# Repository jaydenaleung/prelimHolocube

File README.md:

Holocube
===

A volumetric display from stacked transparent displays as a premise to a true free-floating voxel-array display.

---

## Overview

Holocube is a volumetric (three dimensional) display that utilizes transparent OLED display modules placed on top of each other to create a 128 by 128 by 8 pixel array. The goal of this project is to make a plain, electrical engineering-focused "hologram solution" before attempting to build a more theoretical or physics-based model for three-dimensional displays. The device is primarily run through an Arduino/ESP32-style microcontroller.

**Total time spent: 100+ hrs**

## Why I Created This Project

As suggested above, I am working on a larger personal project to realize three-dimensional display technology (commonly referred to as "holograms"). This provides a simple, stripped-down, preliminary solution to a more complex physics-based approach. Aside from that, it provides an easier solution to popularizing practical three-dimensional technology. Moreover, I simply love sci-fi and holograms and believe in their highly applicable potential, leading me to embark on this project.

## How It Works & Implementation

This device utilizes eight "stacked" transparent OLED displays from the Surenoo dealer on Aliexpress. The transparent OLED displays are driven using 12V external power, 3.3V logic, and SPI communication with an ESP32. The IC within the display is the SH1107 IC. The ESP32 uses either the Adafruit_SH110X + Adafruit_GFX, U8g2_lib, or SPI Arduino IDE library to send the specific SPI commands to drive the OLED panels. The datasheet specifies an external application circuit that includes external capacitors and resistors. See the datasheet for more information. The case was built using the Onshape CAD software.

A log of my testing can be found in the Word document in this repository.

NOTE: The markings on the PCB adapter that come with the transparent OLED display are incorrect. Refer to the PCB for the correct pin markings, with the display output pads always facing up and away from the PCB.

## Rough Bill of Materials (BOM)

| **Name** | **Quantity** | **Price (per part)** | **Link** |
| --- | --- | --- | --- |
| Transparent OLED Display | 8   | $10.15125 | [aliexpress.us/item/3256807797385510.html](https://www.aliexpress.us/item/3256807797385510.html) |
| PCB from JLCPCB | 5 (minimum order qty) | $3.42 | [jlcpcb.com](jlcpcb.com) |
| 30-Pin ESP-32 (28.2 x 51.4 mm) | 1   | $5.11 | [https://www.aliexpress.us/item/3256806034074322.html](https://www.aliexpress.us/item/3256806034074322.html) |
| 12V Power Source/Battery | 1   | $4.87 | [https://www.aliexpress.us/item/3256806309380899.html](https://www.aliexpress.us/item/3256806309380899.html) |
| 1μF Ceramic Capacitor | 8   | $0.033333 | [https://www.amazon.com/BOJACK-Capacitor-Multilayer-Monolithic-Assortment/dp/B085RDTCCV/](https://www.amazon.com/BOJACK-Capacitor-Multilayer-Monolithic-Assortment/dp/B085RDTCCV/) |
| 4.7μF Electrolytic Capacitor | 16  | $0.041667 | [https://www.amazon.com/ALLECIN-Electrolytic-Capacitor-Assortment-Kit/dp/B0C1VBXCQM/](https://www.amazon.com/ALLECIN-Electrolytic-Capacitor-Assortment-Kit/dp/B0C1VBXCQM/) |
| 1MΩ Resistor | 8   | $0.01 | [https://www.amazon.com/BOJACK-Values-Resistor-Resistors-Assortment/dp/B08FD1XVL6/](https://www.amazon.com/BOJACK-Values-Resistor-Resistors-Assortment/dp/B08FD1XVL6/) |

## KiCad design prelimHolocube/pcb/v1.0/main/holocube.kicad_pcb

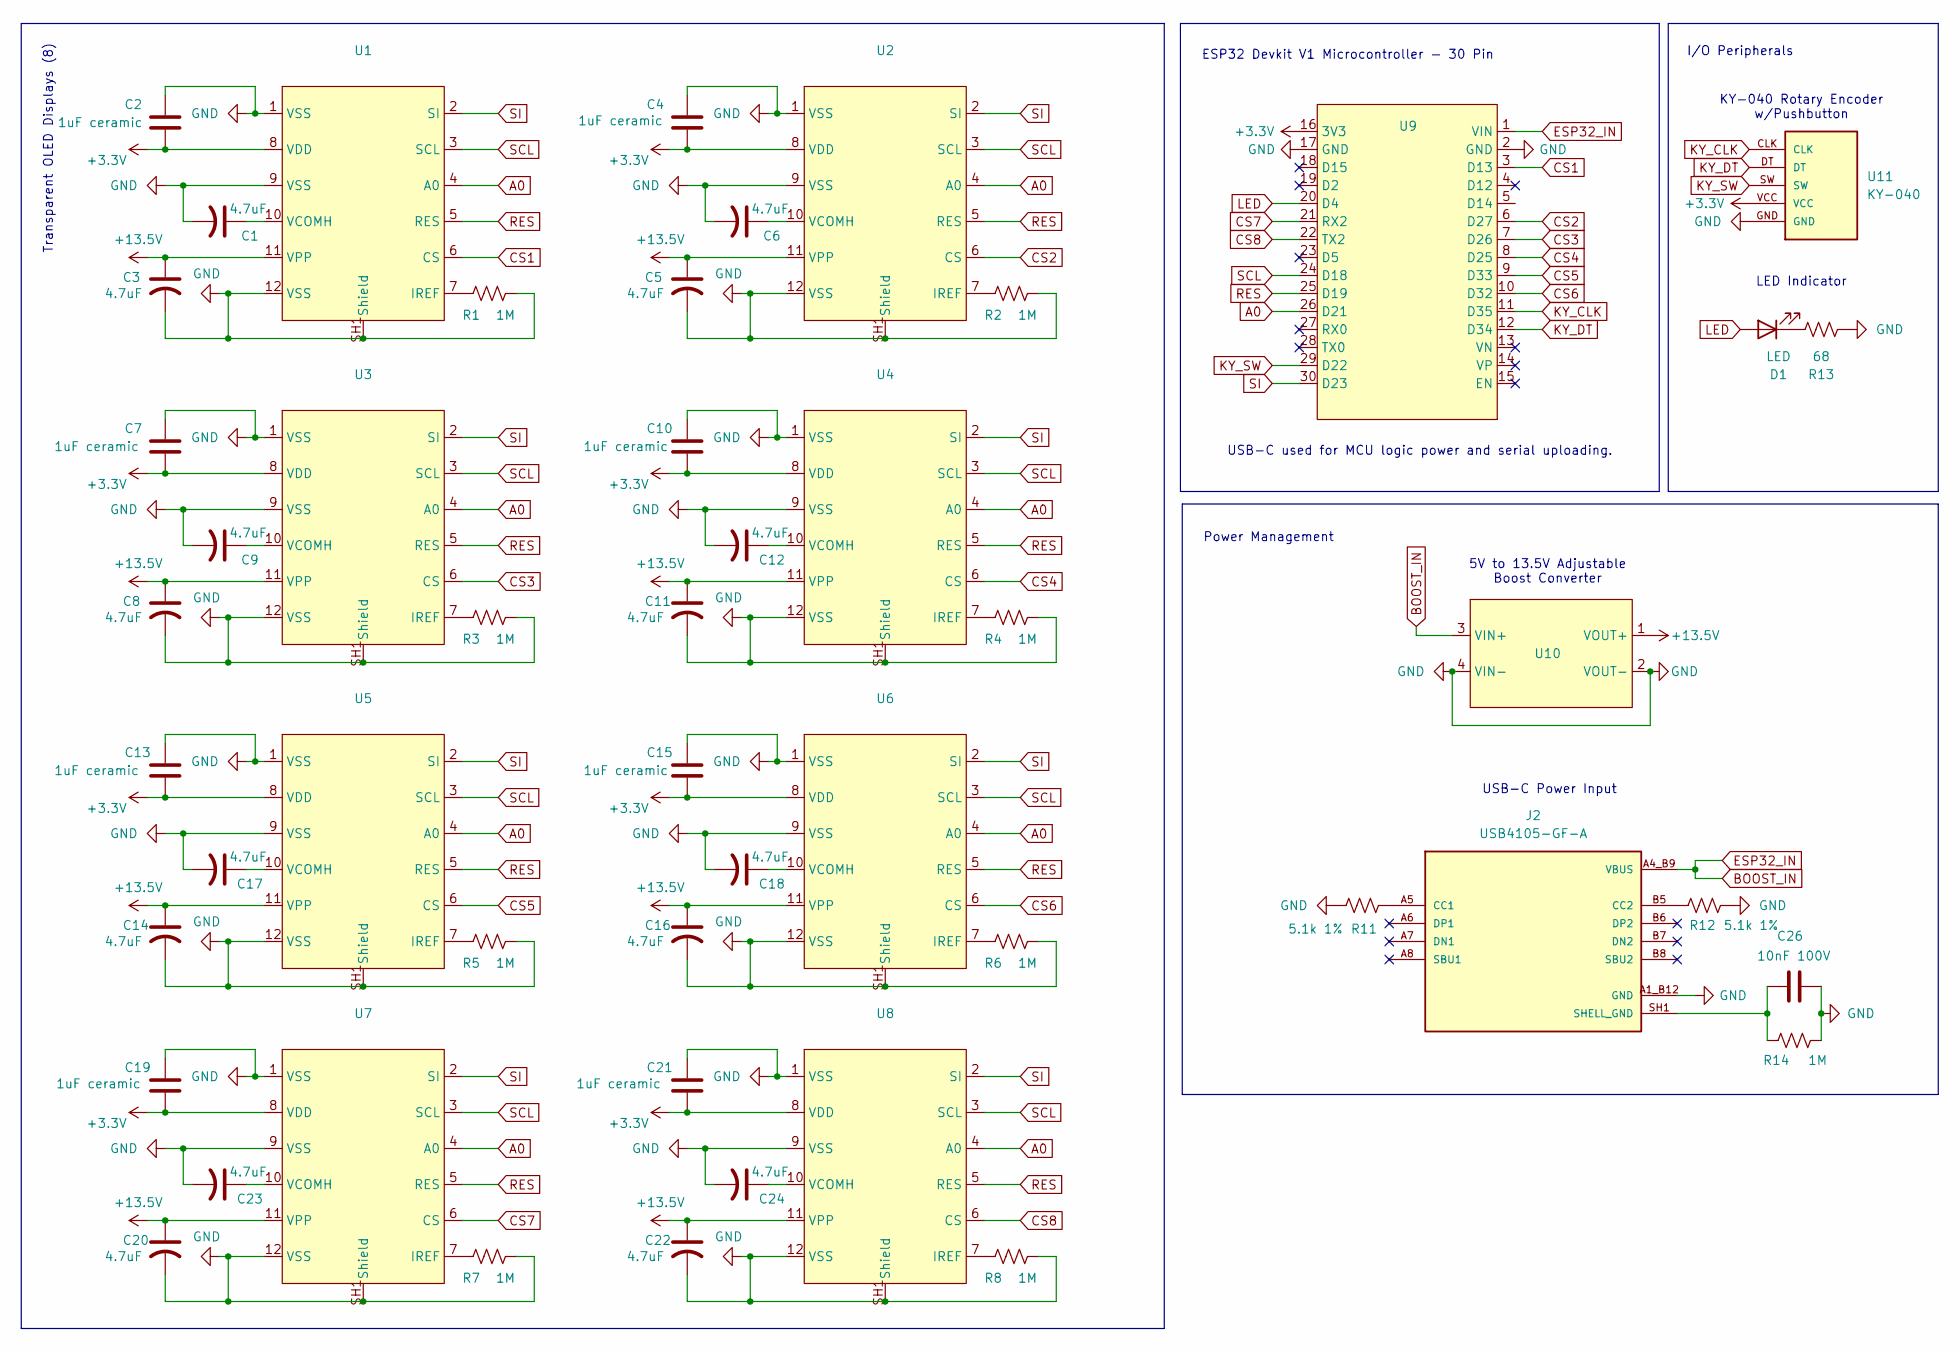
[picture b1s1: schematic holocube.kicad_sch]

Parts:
C1, C3, C5, C6, C8, C9, C11, C12, C14, C16, C17, C18, C20, C22, C23, C24: 4.7uF; CP_Elec_4x5.4
C2, C4, C7, C10, C13, C15, C19, C21: 1uF ceramic; C_0805_2012Metric
C26: 10nF 100V; C_0603_1608Metric
D1: LED; LED_0603_1608Metric
J2: USB4105-GF-A; usbc_connector; PARTREV B4
R1, R2, R3, R4, R5, R6, R7, R8, R14: 1M; R_0805_2012Metric
R11, R12: 5.1k 1%; R_0805_2012Metric
R13: 68; R_0805_2012Metric
U1, U2, U3, U4, U5, U6, U7, U8: AMPHENOL_F31W-1A7H1-11012
U9: devkitv1-30pin
U10: HiLetgo_XL6009_Adjustable
U11: KY-040

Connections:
+3.3V: C2.2, C4.2, C7.2, C10.2, C13.2, C15.2, C19.2, C21.2, U1.8 (VDD), U2.8 (VDD), U3.8 (VDD), U4.8 (VDD), U5.8 (VDD), U6.8 (VDD), U7.8 (VDD), U8.8 (VDD), U9.16 (3V3), U11.VCC
+13.5V: C3.1, C5.1, C8.1, C11.1, C14.1, C16.1, C20.1, C22.1, U1.11 (VPP), U2.11 (VPP), U3.11 (VPP), U4.11 (VPP), U5.11 (VPP), U6.11 (VPP), U7.11 (VPP), U8.11 (VPP), U10.1 (VOUT+)
A0: U1.4 (A0), U2.4 (A0), U3.4 (A0), U4.4 (A0), U5.4 (A0), U6.4 (A0), U7.4 (A0), U8.4 (A0), U9.26 (D21)
BOOST_IN: J2.A4_B9 (VBUS), J2.B4_A9 (VBUS), U9.1 (VIN), U10.3 (VIN+)
CS1: U1.6 (CS), U9.3 (D13)
CS2: U2.6 (CS), U9.6 (D27)
CS3: U3.6 (CS), U9.7 (D26)
CS4: U4.6 (CS), U9.8 (D25)
CS5: U5.6 (CS), U9.9 (D33)
CS6: U6.6 (CS), U9.10 (D32)
CS7: U7.6 (CS), U9.21 (RX2)
CS8: U8.6 (CS), U9.22 (TX2)
GND: C1.2, C2.1, C3.2, C4.1, C5.2, C6.2, C7.1, C8.2, C9.2, C10.1, C11.2, C12.2, C13.1, C14.2, C15.1, C16.2, C17.2, C18.2, C19.1, C20.2, C21.1, C22.2, C23.2, C24.2, C26.2, J2.A1_B12 (GND), J2.B1_A12 (GND), R1.2, R2.2, R3.2, R4.2, R5.2, R6.2, R7.2, R8.2, R11.2, R12.2, R13.2, R14.2, U1.1 (VSS), U1.9 (VSS), U1.12 (VSS), U1.SH1 (Shield), U2.1 (VSS), U2.9 (VSS), U2.12 (VSS), U2.SH1 (Shield), U3.1 (VSS), U3.9 (VSS), U3.12 (VSS), U3.SH1 (Shield), U4.1 (VSS), U4.9 (VSS), U4.12 (VSS), U4.SH1 (Shield), U5.1 (VSS), U5.9 (VSS), U5.12 (VSS), U5.SH1 (Shield), U6.1 (VSS), U6.9 (VSS), U6.12 (VSS), U6.SH1 (Shield), U7.1 (VSS), U7.9 (VSS), U7.12 (VSS), U7.SH1 (Shield), U8.1 (VSS), U8.9 (VSS), U8.12 (VSS), U8.SH1 (Shield), U9.2 (GND), U9.17 (GND), U10.2 (VOUT-), U10.4 (VIN-), U11.GND
KY_CLK: U9.11 (D35), U11.CLK
KY_DT: U9.12 (D34), U11.DT
KY_SW: U9.29 (D22), U11.SW
LED: D1.2 (A), U9.20 (D4)
unnamed: D1.1 (K), R13.1
unnamed: J2.A5 (CC1), R11.1
unnamed: J2.B5 (CC2), R12.1
unnamed: R1.1, U1.7 (IREF)
unnamed: C1.1, U1.10 (VCOMH)
unnamed: R2.1, U2.7 (IREF)
unnamed: C6.1, U2.10 (VCOMH)
unnamed: R3.1, U3.7 (IREF)
unnamed: C9.1, U3.10 (VCOMH)
unnamed: R4.1, U4.7 (IREF)
unnamed: C12.1, U4.10 (VCOMH)
unnamed: R5.1, U5.7 (IREF)
unnamed: C17.1, U5.10 (VCOMH)
unnamed: R6.1, U6.7 (IREF)
unnamed: C18.1, U6.10 (VCOMH)
unnamed: R7.1, U7.7 (IREF)
unnamed: C23.1, U7.10 (VCOMH)
unnamed: R8.1, U8.7 (IREF)
unnamed: C24.1, U8.10 (VCOMH)
RES: U1.5 (RES), U2.5 (RES), U3.5 (RES), U4.5 (RES), U5.5 (RES), U6.5 (RES), U7.5 (RES), U8.5 (RES), U9.25 (D19)
SCL: U1.3 (SCL), U2.3 (SCL), U3.3 (SCL), U4.3 (SCL), U5.3 (SCL), U6.3 (SCL), U7.3 (SCL), U8.3 (SCL), U9.24 (D18)
SHELL_GND: C26.1, J2.SH1 (SHELL_GND), J2.SH2 (SHELL_GND), J2.SH3 (SHELL_GND), J2.SH4 (SHELL_GND), R14.1
SI: U1.2 (SI), U2.2 (SI), U3.2 (SI), U4.2 (SI), U5.2 (SI), U6.2 (SI), U7.2 (SI), U8.2 (SI), U9.30 (D23)

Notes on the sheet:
Transparent OLED Displays (8)
LED Indicator
5V to 13.5V Adjustable Boost Converter
KY-040 Rotary Encoder w/Pushbutton
I/O Peripherals
USB-C used for MCU logic power and serial uploading.
Power Management
ESP32 Devkit V1 Microcontroller - 30 Pin
USB-C Power Input

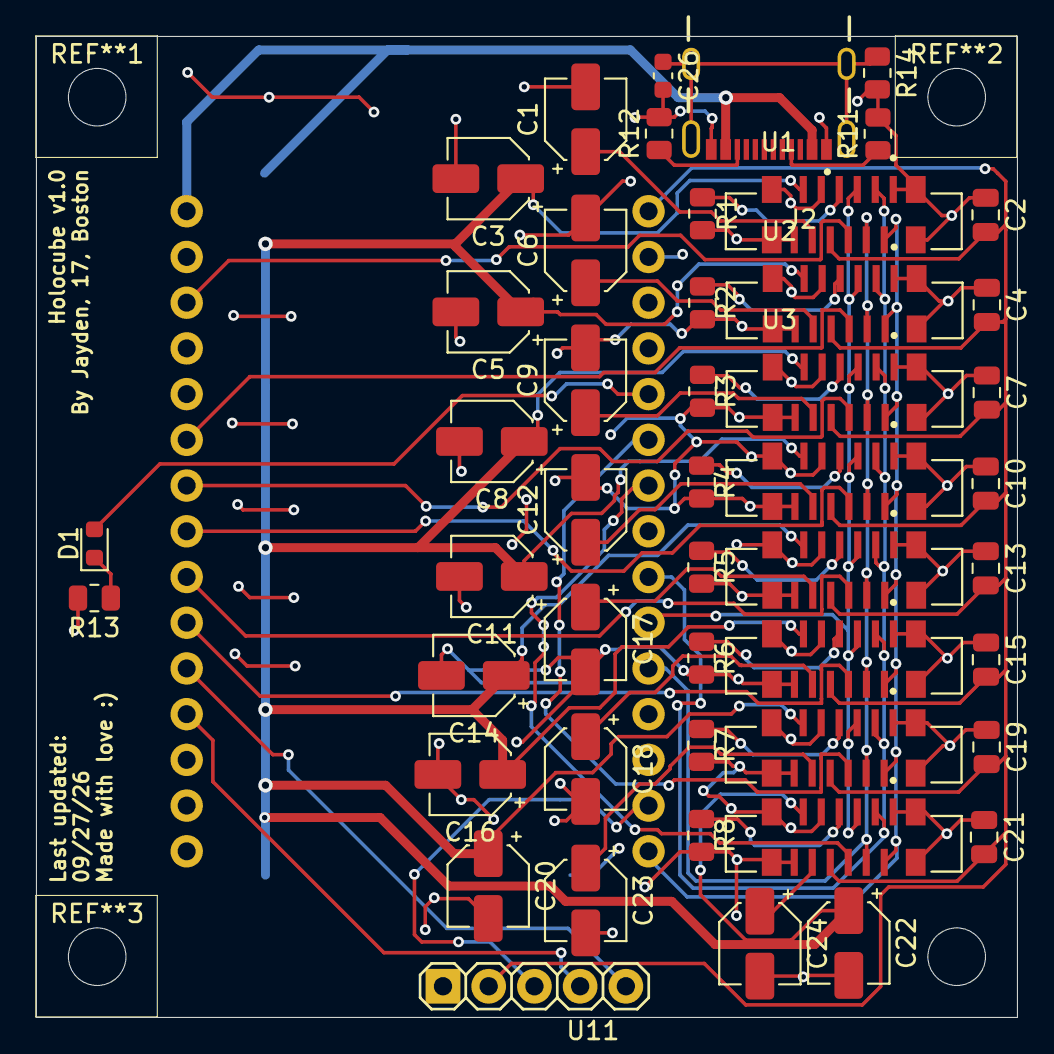
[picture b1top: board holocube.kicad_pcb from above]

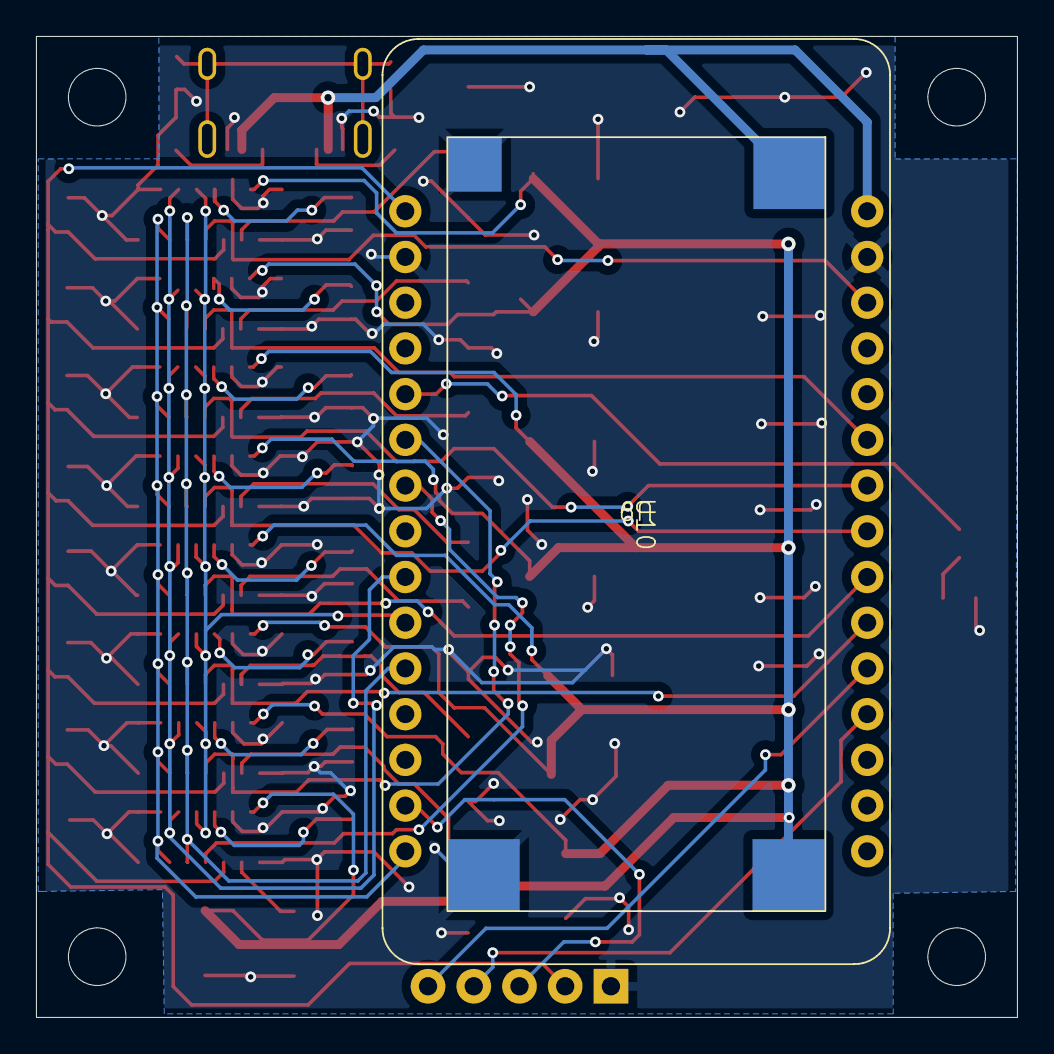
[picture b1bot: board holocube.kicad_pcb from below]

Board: 2 copper layers, 54.5 x 54.5 mm, 50 parts (2 on the bottom side), 40 nets.

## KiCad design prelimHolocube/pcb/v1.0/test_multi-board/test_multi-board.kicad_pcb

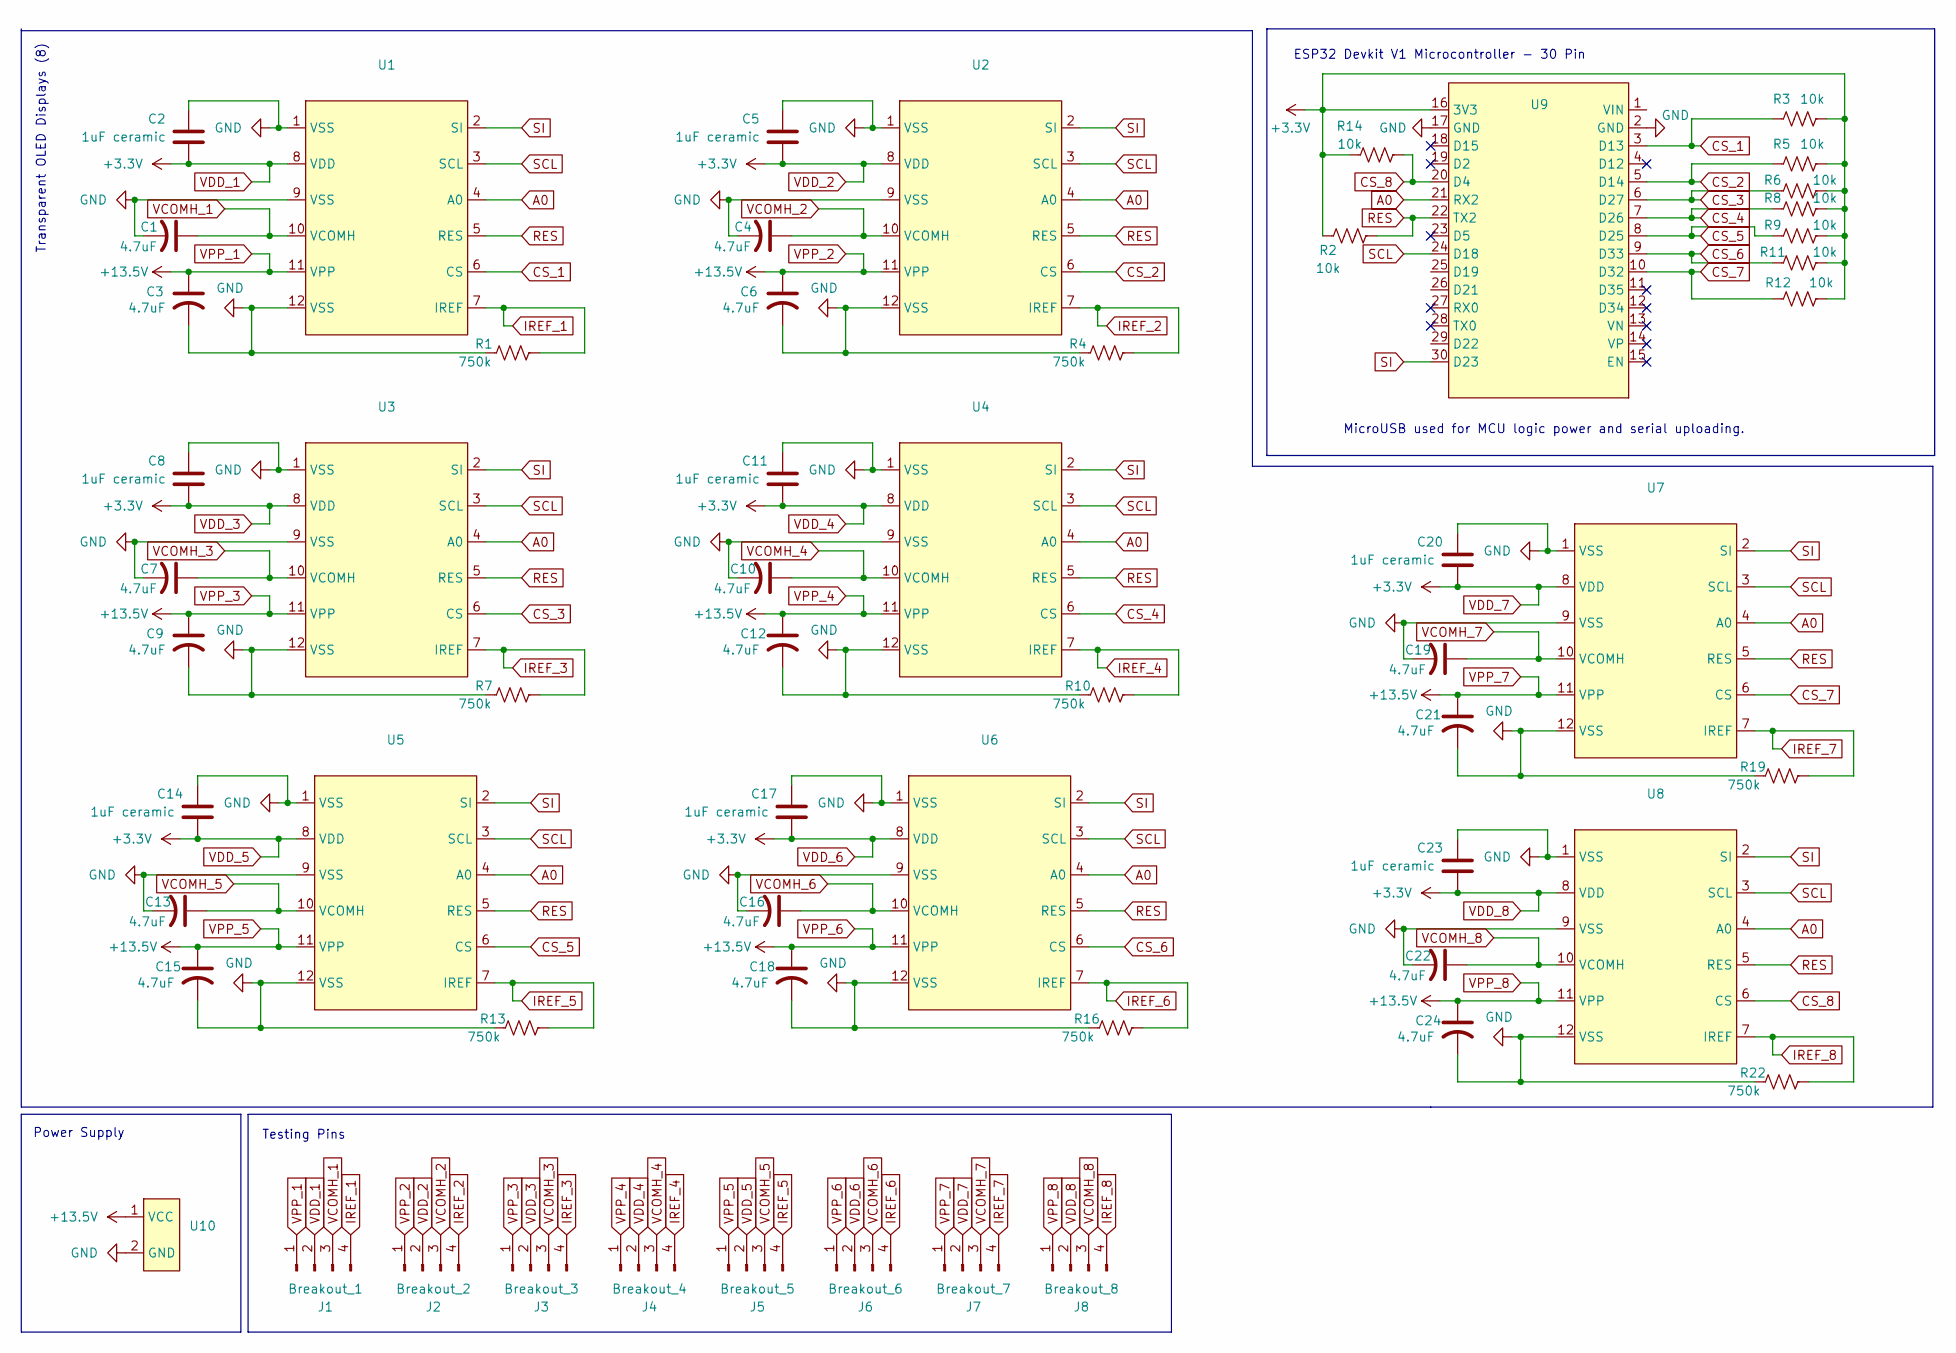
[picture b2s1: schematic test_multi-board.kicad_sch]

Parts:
C1, C3, C4, C6, C7, C9, C10, C12, C13, C15, C16, C18, C19, C21, C22, C24: 4.7uF; CP_Radial_D4.0mm_P2.00mm
C2, C5, C8, C11, C14, C17, C20, C23: 1uF ceramic; C_Disc_D6.0mm_W2.5mm_P5.00mm
J1: Breakout_1; PinHeader_1x04_P2.54mm_Vertical
J2: Breakout_2; PinHeader_1x04_P2.54mm_Vertical
J3: Breakout_3; PinHeader_1x04_P2.54mm_Vertical
J4: Breakout_4; PinHeader_1x04_P2.54mm_Vertical
J5: Breakout_5; PinHeader_1x04_P2.54mm_Vertical
J6: Breakout_6; PinHeader_1x04_P2.54mm_Vertical
J7: Breakout_7; PinHeader_1x04_P2.54mm_Vertical
J8: Breakout_8; PinHeader_1x04_P2.54mm_Vertical
R1, R4, R7, R10, R13, R16, R19, R22: 750k; R_Axial_DIN0207_L6.3mm_D2.5mm_P7.62mm_Horizontal
R2, R3, R5, R6, R8, R9, R11, R12, R14: 10k; R_Axial_DIN0207_L6.3mm_D2.5mm_P7.62mm_Horizontal
U1, U2, U3, U4, U5, U6, U7, U8: surenoo-1.12in-128x128
U9: devkitv1-30pin
U10: PinHeader_1x02_P2.54mm_Vertical

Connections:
A0: U1.4 (A0), U2.4 (A0), U3.4 (A0), U4.4 (A0), U5.4 (A0), U6.4 (A0), U7.4 (A0), U8.4 (A0), U9.21 (RX2)
CS_1: R3.1, U1.6 (CS), U9.3 (D13)
CS_2: R5.1, U2.6 (CS), U9.5 (D14)
CS_3: R6.1, U3.6 (CS), U9.6 (D27)
CS_4: R8.1, U4.6 (CS), U9.7 (D26)
CS_5: R9.1, U5.6 (CS), U9.8 (D25)
CS_6: R11.1, U6.6 (CS), U9.9 (D33)
CS_7: R12.1, U7.6 (CS), U9.10 (D32)
CS_8: R14.1, U8.6 (CS), U9.20 (D4)
GND: C1.2, C2.1, C3.2, C4.2, C5.1, C6.2, C7.2, C8.1, C9.2, C10.2, C11.1, C12.2, C13.2, C14.1, C15.2, C16.2, C17.1, C18.2, C19.2, C20.1, C21.2, C22.2, C23.1, C24.2, R1.1, R4.1, R7.1, R10.1, R13.1, R16.1, R19.1, R22.1, U1.1 (VSS), U1.9 (VSS), U1.12 (VSS), U2.1 (VSS), U2.9 (VSS), U2.12 (VSS), U3.1 (VSS), U3.9 (VSS), U3.12 (VSS), U4.1 (VSS), U4.9 (VSS), U4.12 (VSS), U5.1 (VSS), U5.9 (VSS), U5.12 (VSS), U6.1 (VSS), U6.9 (VSS), U6.12 (VSS), U7.1 (VSS), U7.9 (VSS), U7.12 (VSS), U8.1 (VSS), U8.9 (VSS), U8.12 (VSS), U9.2 (GND), U9.17 (GND), U10.2 (GND)
IREF_1: J1.4, R1.2, U1.7 (IREF)
IREF_2: J2.4, R4.2, U2.7 (IREF)
IREF_3: J3.4, R7.2, U3.7 (IREF)
IREF_4: J4.4, R10.2, U4.7 (IREF)
IREF_5: J5.4, R13.2, U5.7 (IREF)
IREF_6: J6.4, R16.2, U6.7 (IREF)
IREF_7: J7.4, R19.2, U7.7 (IREF)
IREF_8: J8.4, R22.2, U8.7 (IREF)
RES: R2.1, U1.5 (RES), U2.5 (RES), U3.5 (RES), U4.5 (RES), U5.5 (RES), U6.5 (RES), U7.5 (RES), U8.5 (RES), U9.22 (TX2)
SCL: U1.3 (SCL), U2.3 (SCL), U3.3 (SCL), U4.3 (SCL), U5.3 (SCL), U6.3 (SCL), U7.3 (SCL), U8.3 (SCL), U9.24 (D18)
SI: U1.2 (SI), U2.2 (SI), U3.2 (SI), U4.2 (SI), U5.2 (SI), U6.2 (SI), U7.2 (SI), U8.2 (SI), U9.30 (D23)
VCOMH_1: C1.1, J1.3, U1.10 (VCOMH)
VCOMH_2: C4.1, J2.3, U2.10 (VCOMH)
VCOMH_3: C7.1, J3.3, U3.10 (VCOMH)
VCOMH_4: C10.1, J4.3, U4.10 (VCOMH)
VCOMH_5: C13.1, J5.3, U5.10 (VCOMH)
VCOMH_6: C16.1, J6.3, U6.10 (VCOMH)
VCOMH_7: C19.1, J7.3, U7.10 (VCOMH)
VCOMH_8: C22.1, J8.3, U8.10 (VCOMH)
VDD_1: C2.2, C5.2, C8.2, C11.2, C14.2, C17.2, C20.2, C23.2, J1.2, J2.2, J3.2, J4.2, J5.2, J6.2, J7.2, J8.2, R2.2, R3.2, R5.2, R6.2, R8.2, R9.2, R11.2, R12.2, R14.2, U1.8 (VDD), U2.8 (VDD), U3.8 (VDD), U4.8 (VDD), U5.8 (VDD), U6.8 (VDD), U7.8 (VDD), U8.8 (VDD), U9.16 (3V3)
VPP_1: C3.1, C6.1, C9.1, C12.1, C15.1, C18.1, C21.1, C24.1, J1.1, J2.1, J3.1, J4.1, J5.1, J6.1, J7.1, J8.1, U1.11 (VPP), U2.11 (VPP), U3.11 (VPP), U4.11 (VPP), U5.11 (VPP), U6.11 (VPP), U7.11 (VPP), U8.11 (VPP), U10.1 (VCC)

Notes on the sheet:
ESP32 Devkit V1 Microcontroller - 30 Pin
Transparent OLED Displays (8)
Power Supply
MicroUSB used for MCU logic power and serial uploading.
Testing Pins

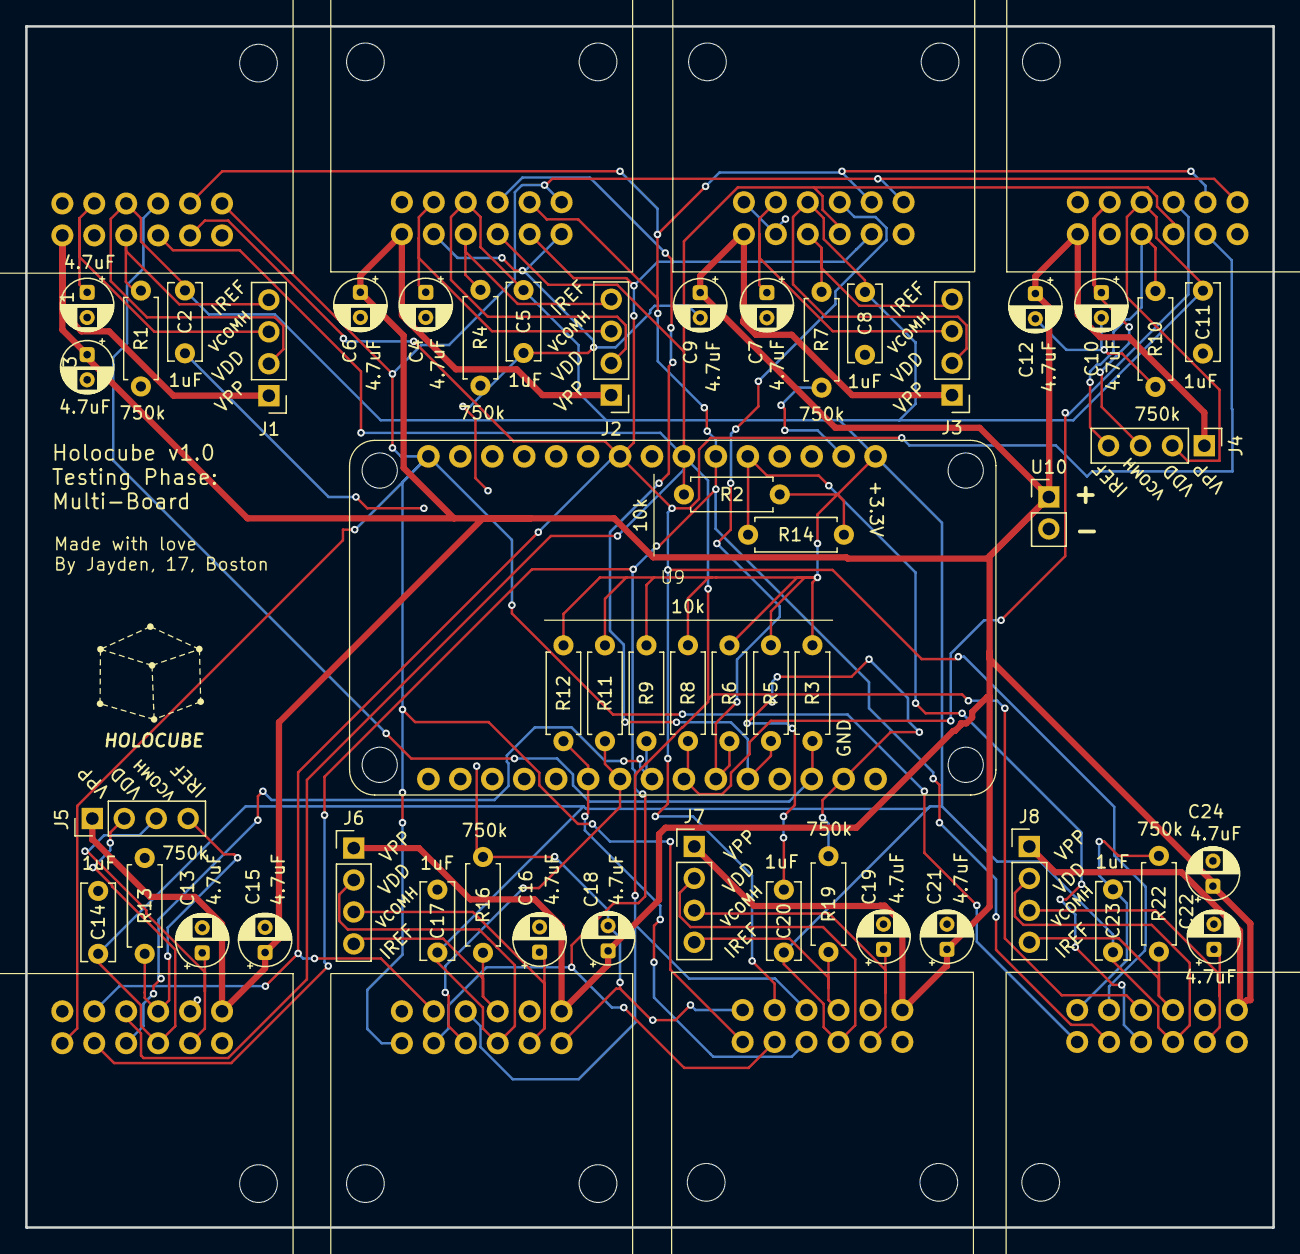
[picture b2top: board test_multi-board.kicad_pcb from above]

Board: 2 copper layers, 99.2 x 95.5 mm, 59 parts (0 on the bottom side), 31 nets.

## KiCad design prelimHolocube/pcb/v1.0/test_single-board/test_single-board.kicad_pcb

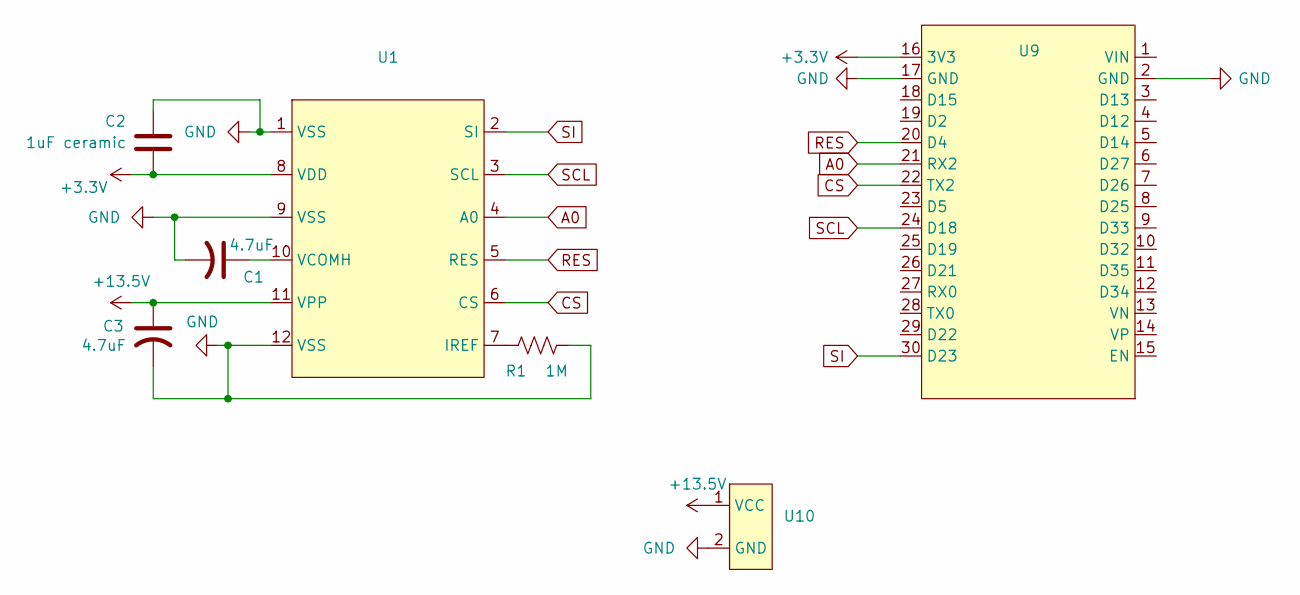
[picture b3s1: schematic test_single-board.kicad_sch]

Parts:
C1, C3: 4.7uF; CP_Radial_D4.0mm_P2.00mm
C2: 1uF ceramic; C_Disc_D6.0mm_W2.5mm_P5.00mm
R1: 1M; R_Axial_DIN0207_L6.3mm_D2.5mm_P7.62mm_Horizontal
U1: surenoo-1.12in-128x128
U9: devkitv1-30pin
U10: PinHeader_1x02_P2.54mm_Vertical

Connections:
+3.3V: C2.2, U1.8 (VDD), U9.16 (3V3)
+13.5V: C3.1, U1.11 (VPP), U10.1 (VCC)
A0: U1.4 (A0), U9.21 (RX2)
CS: U1.6 (CS), U9.22 (TX2)
GND: C1.2, C2.1, C3.2, R1.2, U1.1 (VSS), U1.9 (VSS), U1.12 (VSS), U9.2 (GND), U9.17 (GND), U10.2 (GND)
unnamed: R1.1, U1.7 (IREF)
unnamed: C1.1, U1.10 (VCOMH)
RES: U1.5 (RES), U9.20 (D4)
SCL: U1.3 (SCL), U9.24 (D18)
SI: U1.2 (SI), U9.30 (D23)

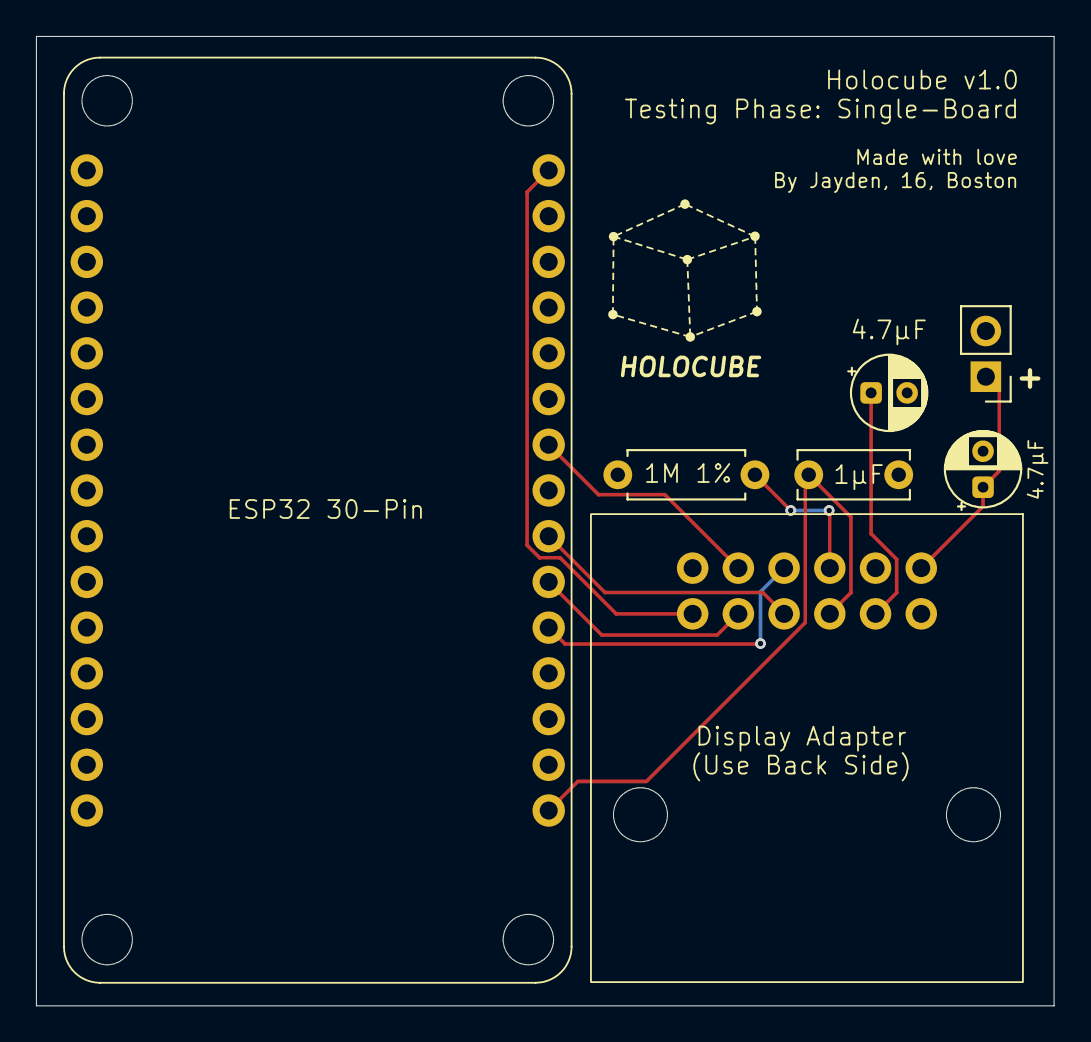
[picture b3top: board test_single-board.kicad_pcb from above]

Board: 2 copper layers, 56.5 x 53.9 mm, 7 parts (0 on the bottom side), 10 nets.

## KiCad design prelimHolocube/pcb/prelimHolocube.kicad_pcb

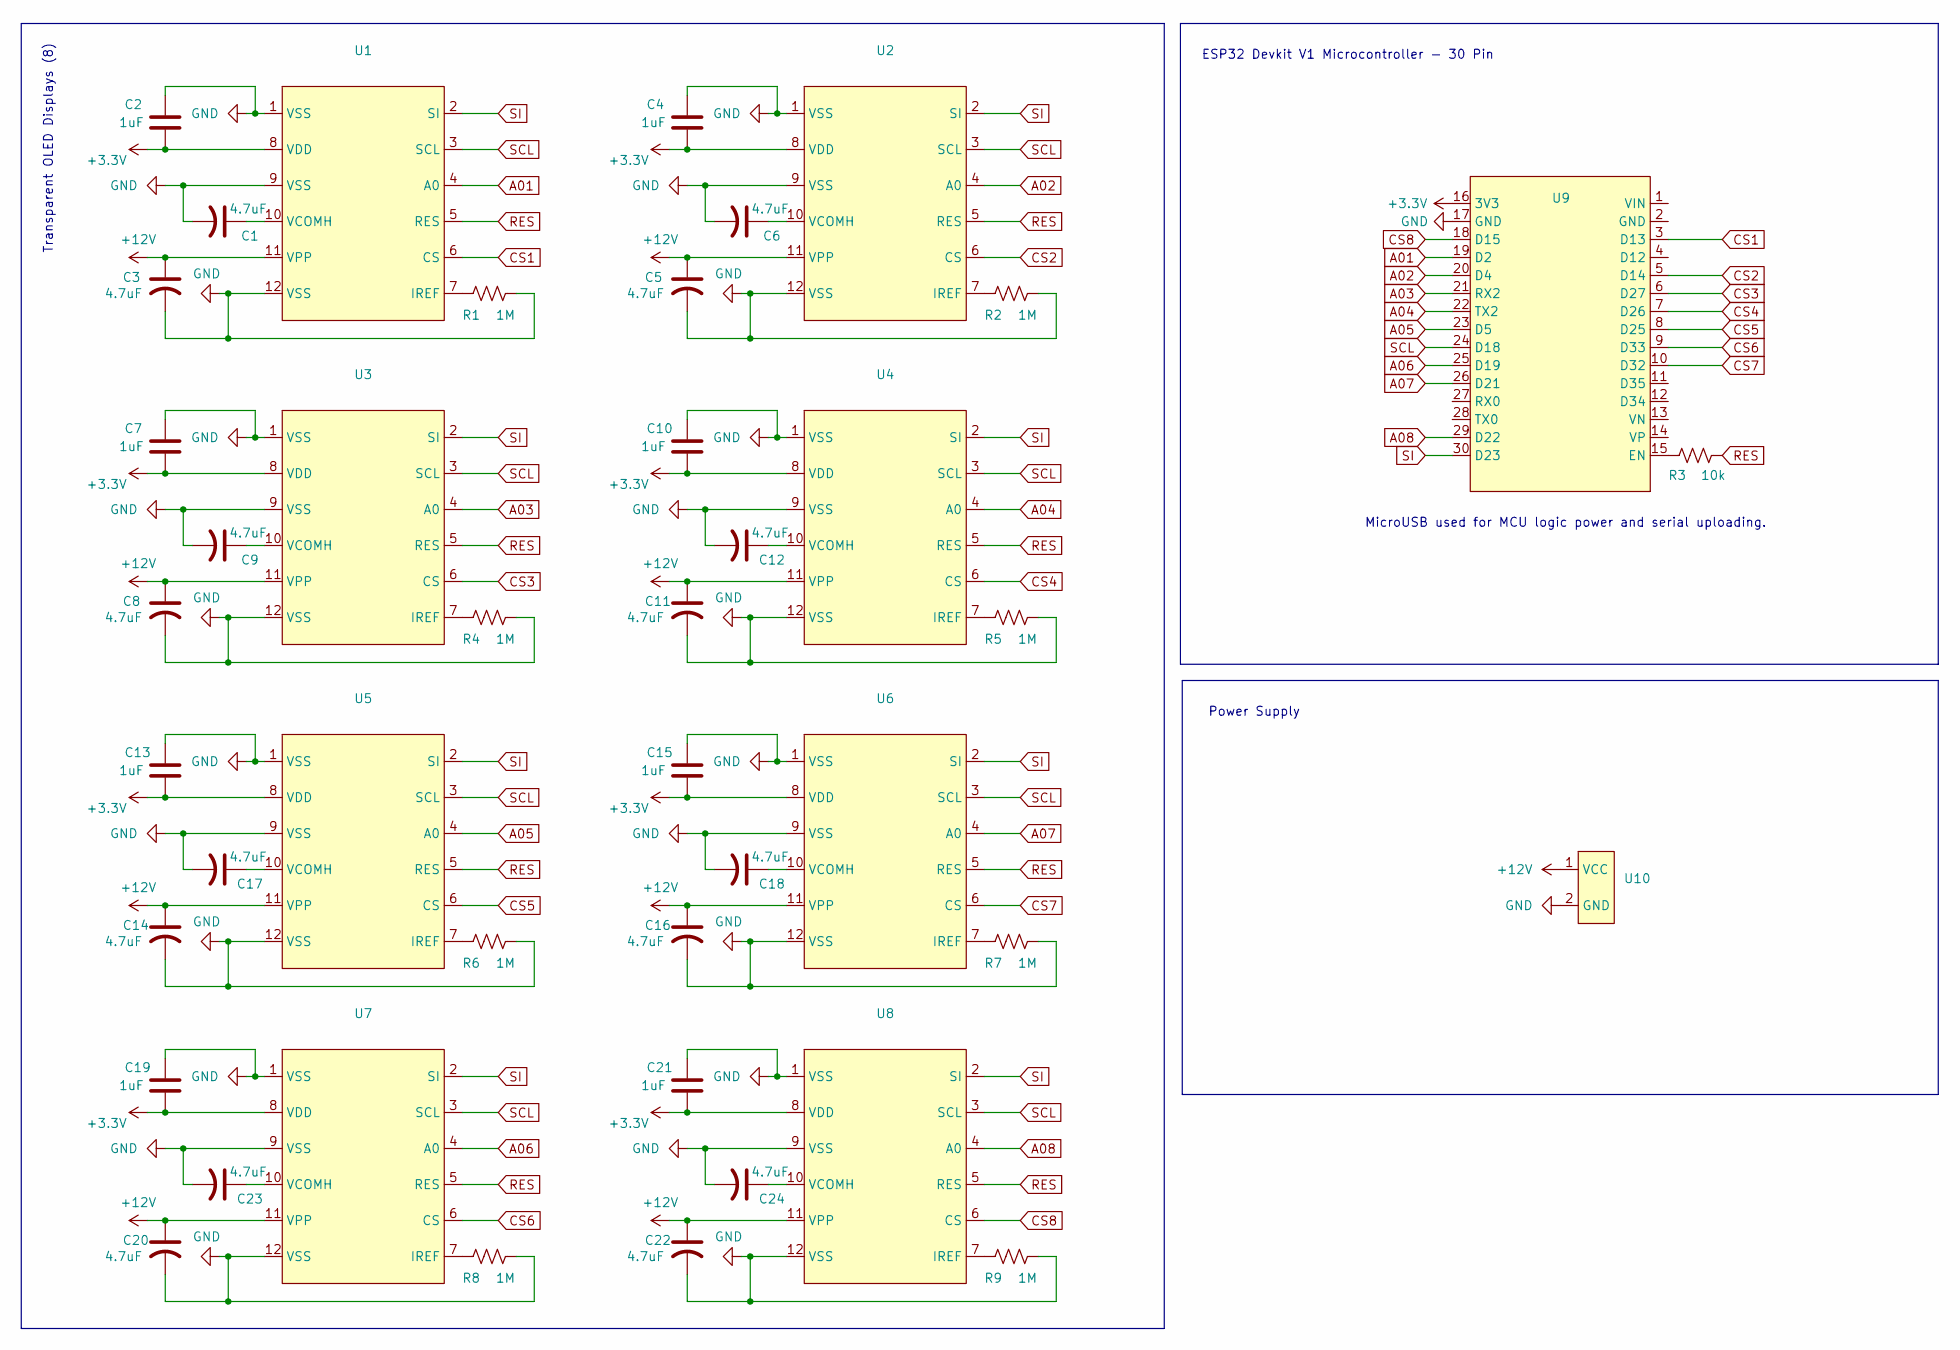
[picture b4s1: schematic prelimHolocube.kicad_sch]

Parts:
C1, C3, C5, C6, C8, C9, C11, C12, C14, C16, C17, C18, C20, C22, C23, C24: 4.7uF; CP_Radial_D4.0mm_P2.00mm
C2, C4, C7, C10, C13, C15, C19, C21: 1uF; CP_Radial_D5.0mm_P2.50mm
R1, R2, R4, R5, R6, R7, R8, R9: 1M; R_Axial_DIN0207_L6.3mm_D2.5mm_P7.62mm_Horizontal
R3: 10k; R_Axial_DIN0207_L6.3mm_D2.5mm_P7.62mm_Horizontal
U1, U2, U3, U4, U5, U6, U7, U8: surenoo-1.12in-128x128
U9: devkitv1-30pin
U10: DC_2-Terminals

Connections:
+3.3V: C2.2, C4.2, C7.2, C10.2, C13.2, C15.2, C19.2, C21.2, U1.8 (VDD), U2.8 (VDD), U3.8 (VDD), U4.8 (VDD), U5.8 (VDD), U6.8 (VDD), U7.8 (VDD), U8.8 (VDD), U9.16 (3V3)
+12V: C3.1, C5.1, C8.1, C11.1, C14.1, C16.1, C20.1, C22.1, U1.11 (VPP), U2.11 (VPP), U3.11 (VPP), U4.11 (VPP), U5.11 (VPP), U6.11 (VPP), U7.11 (VPP), U8.11 (VPP), U10.1 (VCC)
A01: U1.4 (A0), U9.19 (D2)
A02: U2.4 (A0), U9.20 (D4)
A03: U3.4 (A0), U9.21 (RX2)
A04: U4.4 (A0), U9.22 (TX2)
A05: U5.4 (A0), U9.23 (D5)
A06: U7.4 (A0), U9.25 (D19)
A07: U6.4 (A0), U9.26 (D21)
A08: U8.4 (A0), U9.29 (D22)
CS1: U1.6 (CS), U9.3 (D13)
CS2: U2.6 (CS), U9.5 (D14)
CS3: U3.6 (CS), U9.6 (D27)
CS4: U4.6 (CS), U9.7 (D26)
CS5: U5.6 (CS), U9.8 (D25)
CS6: U7.6 (CS), U9.9 (D33)
CS7: U6.6 (CS), U9.10 (D32)
CS8: U8.6 (CS), U9.18 (D15)
GND: C1.2, C2.1, C3.2, C4.1, C5.2, C6.2, C7.1, C8.2, C9.2, C10.1, C11.2, C12.2, C13.1, C14.2, C15.1, C16.2, C17.2, C18.2, C19.1, C20.2, C21.1, C22.2, C23.2, C24.2, R1.2, R2.2, R4.2, R5.2, R6.2, R7.2, R8.2, R9.2, U1.1 (VSS), U1.9 (VSS), U1.12 (VSS), U2.1 (VSS), U2.9 (VSS), U2.12 (VSS), U3.1 (VSS), U3.9 (VSS), U3.12 (VSS), U4.1 (VSS), U4.9 (VSS), U4.12 (VSS), U5.1 (VSS), U5.9 (VSS), U5.12 (VSS), U6.1 (VSS), U6.9 (VSS), U6.12 (VSS), U7.1 (VSS), U7.9 (VSS), U7.12 (VSS), U8.1 (VSS), U8.9 (VSS), U8.12 (VSS), U9.17 (GND), U10.2 (GND); also elsewhere on the board
unnamed: R1.1, U1.7 (IREF)
unnamed: C1.1, U1.10 (VCOMH)
unnamed: R2.1, U2.7 (IREF)
unnamed: C6.1, U2.10 (VCOMH)
unnamed: R4.1, U3.7 (IREF)
unnamed: C9.1, U3.10 (VCOMH)
unnamed: R5.1, U4.7 (IREF)
unnamed: C12.1, U4.10 (VCOMH)
unnamed: R6.1, U5.7 (IREF)
unnamed: C17.1, U5.10 (VCOMH)
unnamed: R7.1, U6.7 (IREF)
unnamed: C18.1, U6.10 (VCOMH)
unnamed: R8.1, U7.7 (IREF)
unnamed: C23.1, U7.10 (VCOMH)
unnamed 33: R9.1, U8.7 (IREF); also elsewhere on the board
unnamed: C24.1, U8.10 (VCOMH)
unnamed: R3.1, U9.15 (EN)
RES: R3.2, U1.5 (RES), U2.5 (RES), U3.5 (RES), U4.5 (RES), U5.5 (RES), U6.5 (RES), U7.5 (RES), U8.5 (RES)
SCL: U1.3 (SCL), U2.3 (SCL), U3.3 (SCL), U4.3 (SCL), U5.3 (SCL), U6.3 (SCL), U7.3 (SCL), U8.3 (SCL), U9.24 (D18)
SI: U1.2 (SI), U2.2 (SI), U3.2 (SI), U4.2 (SI), U5.2 (SI), U6.2 (SI), U7.2 (SI), U8.2 (SI), U9.30 (D23)

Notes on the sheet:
ESP32 Devkit V1 Microcontroller - 30 Pin
Transparent OLED Displays (8)
Power Supply
MicroUSB used for MCU logic power and serial uploading.
